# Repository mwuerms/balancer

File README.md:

# balancer
self balancing robot

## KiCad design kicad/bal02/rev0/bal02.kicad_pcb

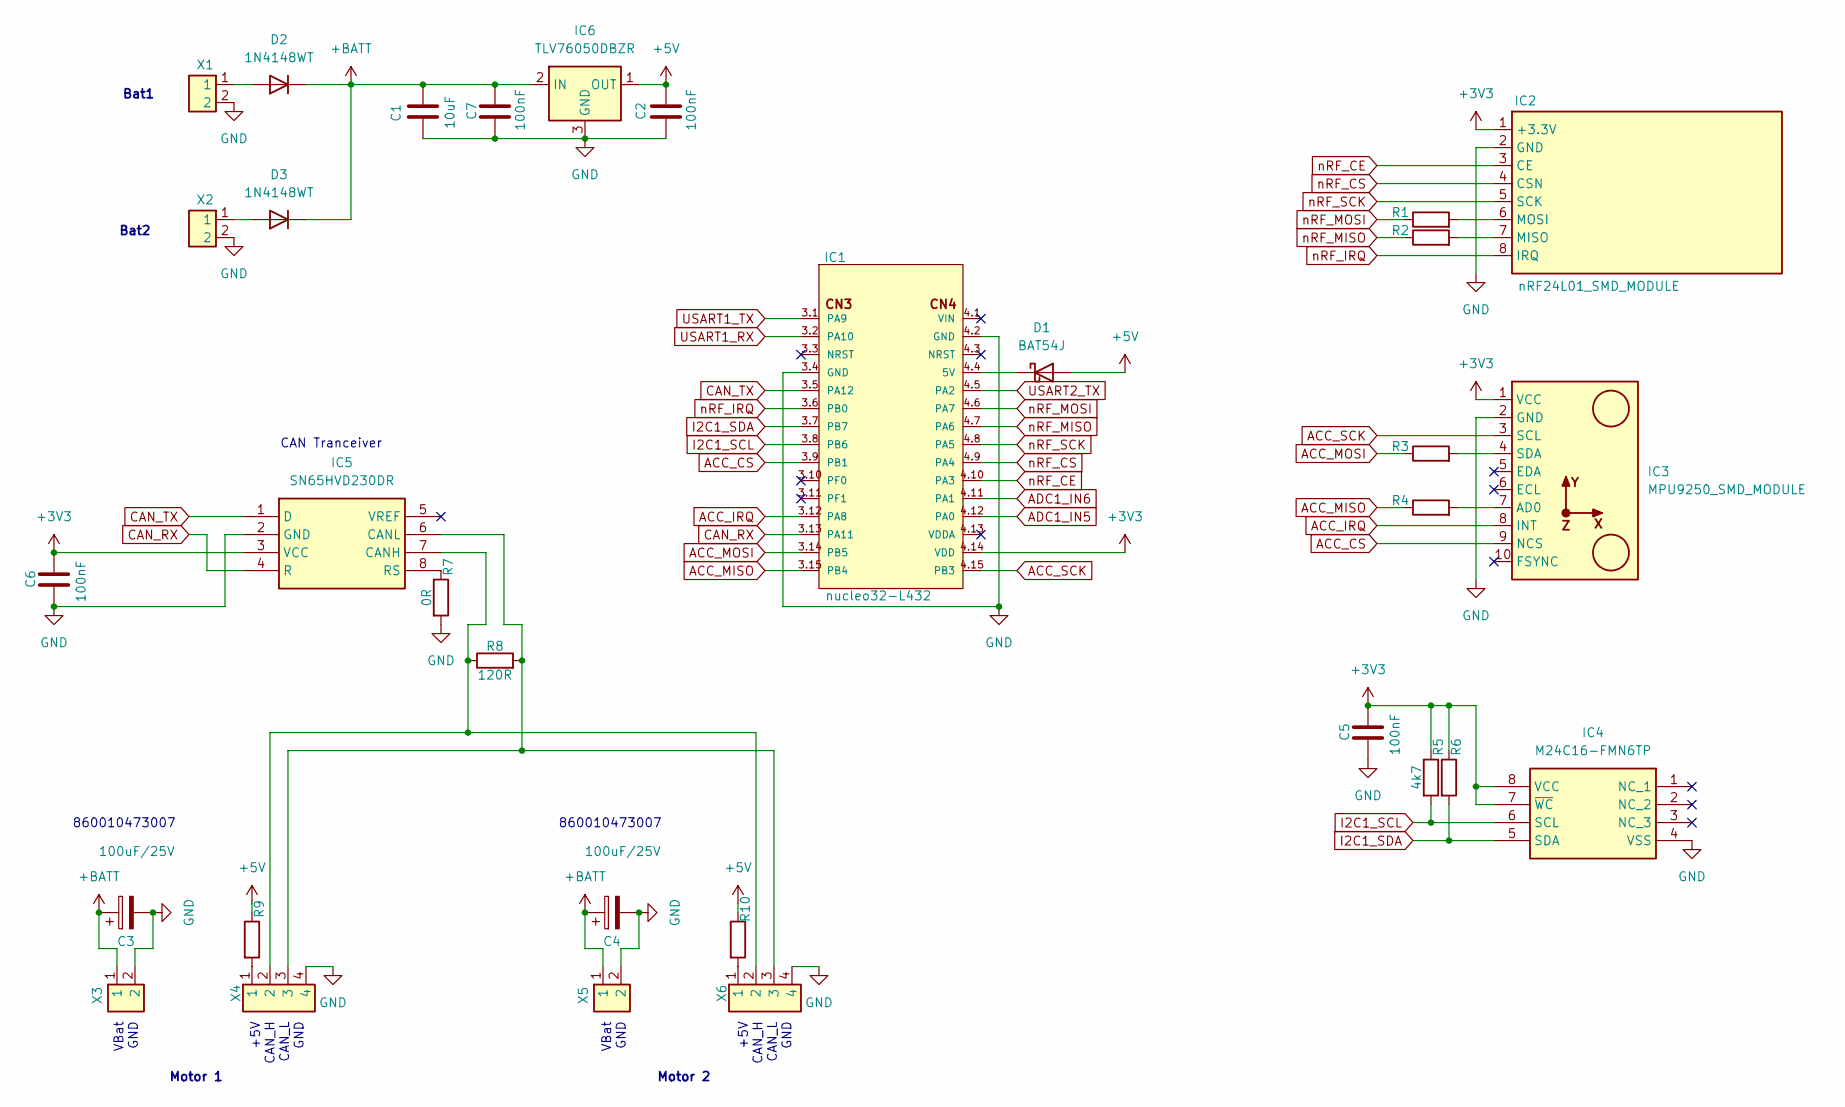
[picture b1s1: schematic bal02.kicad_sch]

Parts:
C1: 10uF; C_0805_2012Metric
C2, C5, C6, C7: 100nF; C_0603_1608Metric
C3, C4: 100uF/25V; WCAP-ATG8
D1: BAT54J; D_SOD-323F
D2, D3: 1N4148WT; D_SOD-523
IC1: nucleo32-L432; nucleo32; PARTREV 3
IC2: nRF24L01_SMD_MODULE
IC3: MPU9250_SMD_MODULE
IC4: M24C16-FMN6TP; SOIC127P600X175-8N; Manufacturer_Part_Number M24C16-FMN6TP; Mouser Part Number 511-M24C16-FMN6TP
IC5: SN65HVD230DR; SOT127P600X175-8N; Manufacturer_Part_Number SN65HVD230DR; Mouser Part Number 595-SN65HVD230DR
IC6: TLV76050DBZR; SOT95P237X112-3N; Manufacturer_Part_Number TLV76050DBZR; Mouser Part Number 595-TLV76050DBZR
R1, R2, R3, R4, R9, R10: R; R_0402_1005Metric
R5, R6: 4k7; R_0603_1608Metric
R7: 0R; R_0603_1608Metric
R8: 120R; R_0603_1608Metric
X1, X2, X3, X5: H2_100mil
X4, X6: H4_50mil

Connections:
+3V3: C5.1, C6.1, IC1.4.14 (VDD), IC2.1 (+3.3V), IC3.1 (VCC), IC4.7 (~WC), IC4.8 (VCC), IC5.3 (VCC), R5.1, R6.1
+5V: C2.1, D1.2 (A), IC6.1 (OUT), R9.1, R10.1
+BATT: C1.1, C3.1, C4.1, C7.1, D2.1 (K), D3.1 (K), IC6.2 (IN), X3.1, X5.1
ACC_CS: IC1.3.9 (PB1), IC3.9 (NCS)
ACC_IRQ: IC1.3.12 (PA8), IC3.8 (INT)
ACC_MISO: IC1.3.15 (PB4), R4.1
ACC_MOSI: IC1.3.14 (PB5), R3.1
ACC_SCK: IC1.4.15 (PB3), IC3.3 (SCL)
ADC1_IN5: IC1.4.12 (PA0)
ADC1_IN6: IC1.4.11 (PA1)
CAN_RX: IC1.3.13 (PA11), IC5.4 (R)
CAN_TX: IC1.3.5 (PA12), IC5.1 (D)
GND: C1.2, C2.2, C3.2, C4.2, C5.2, C6.2, C7.2, IC1.3.4 (GND), IC1.4.2 (GND), IC2.2 (GND), IC3.2 (GND), IC4.4 (VSS), IC5.2 (GND), IC6.3 (GND), R7.2, X1.2, X2.2, X3.2, X4.4, X5.2, X6.4
I2C1_SCL: IC1.3.8 (PB6), IC4.6 (SCL), R5.2
I2C1_SDA: IC1.3.7 (PB7), IC4.5 (SDA), R6.2
unnamed: D1.1 (K), IC1.4.4 (5V)
unnamed: D2.2 (A), X1.1
unnamed: D3.2 (A), X2.1
unnamed: IC2.7 (MISO), R2.2
unnamed: IC2.6 (MOSI), R1.2
unnamed: IC3.7 (AD0), R4.2
unnamed: IC3.4 (SDA), R3.2
unnamed: IC5.7 (CANH), R8.1, X4.2, X6.2
unnamed: IC5.6 (CANL), R8.2, X4.3, X6.3
unnamed: IC5.8 (RS), R7.1
unnamed: R9.2, X4.1
unnamed: R10.2, X6.1
USART1_RX: IC1.3.2 (PA10)
USART1_TX: IC1.3.1 (PA9)
USART2_TX: IC1.4.5 (PA2)
nRF_CE: IC1.4.10 (PA3), IC2.3 (CE)
nRF_CS: IC1.4.9 (PA4), IC2.4 (CSN)
nRF_IRQ: IC1.3.6 (PB0), IC2.8 (IRQ)
nRF_MISO: IC1.4.7 (PA6), R2.1
nRF_MOSI: IC1.4.6 (PA7), R1.1
nRF_SCK: IC1.4.8 (PA5), IC2.5 (SCK)

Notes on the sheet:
Bat2
Bat1
860010473007
+5V CAN_H CAN_L GND
VBat GND
Motor 2
CAN Tranceiver
Motor 1

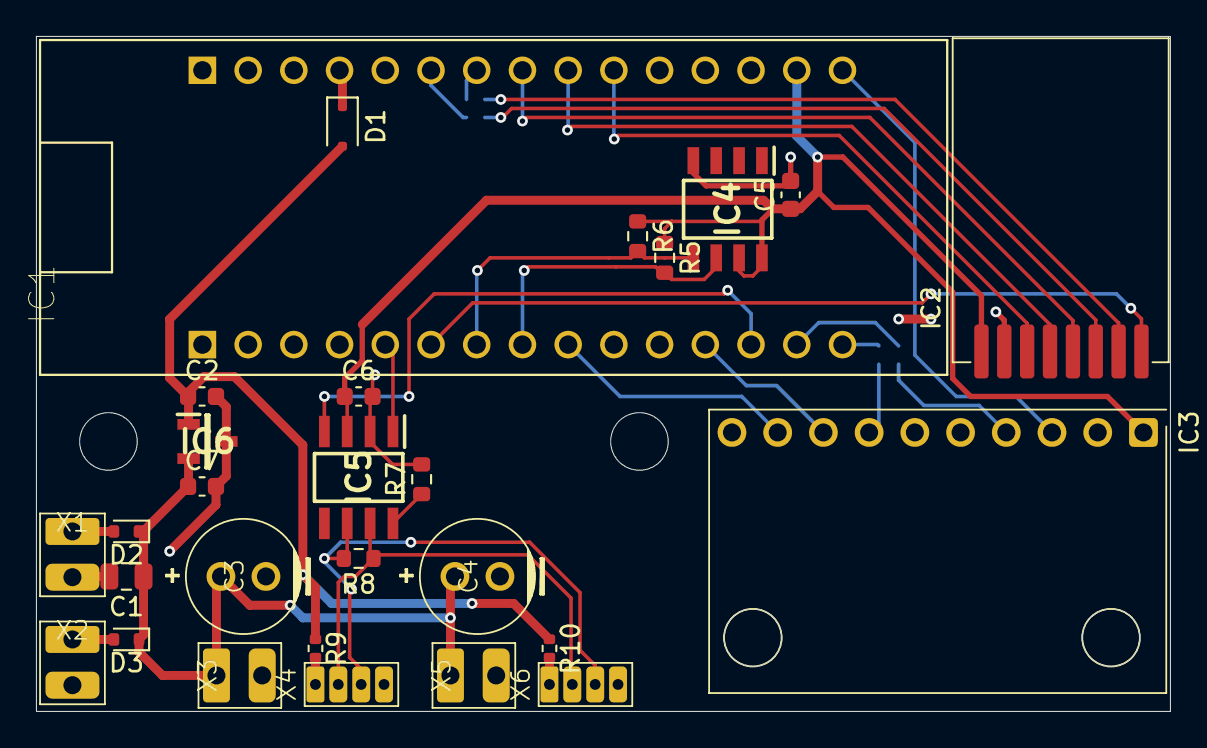
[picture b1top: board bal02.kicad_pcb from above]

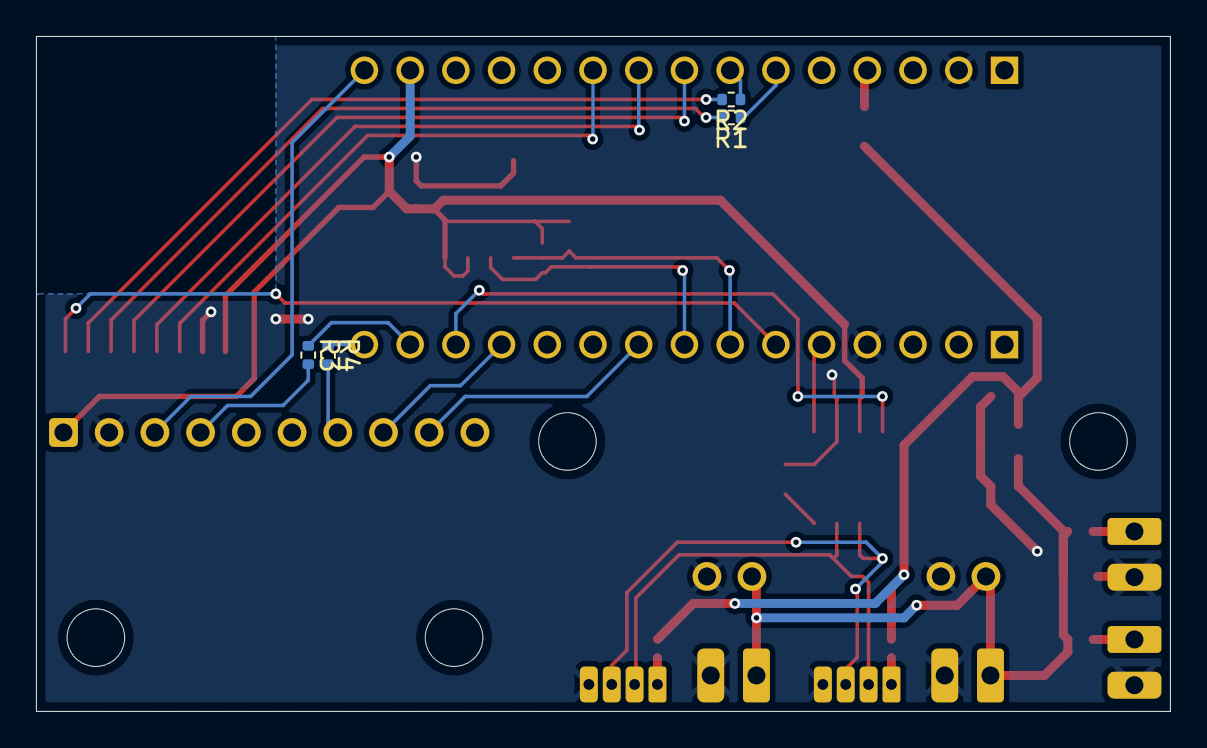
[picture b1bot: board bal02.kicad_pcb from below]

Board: 2 copper layers, 63.0 x 37.5 mm, 32 parts (4 on the bottom side), 31 nets.

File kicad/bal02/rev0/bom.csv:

Designator,Footprint,Quantity,Value,LCSC Part #
C1,0805,1,10uF,
"C2, C5, C6, C7",0603,4,100nF,
"C3, C4",WCAP-ATG8,2,100uF/25V,
D1,D_SOD-323F,1,BAT54J,
"D2, D3",D_SOD-523,2,1N4148WT,
IC1,nucleo32,1,nucleo32-L432,
IC2,nRF24L01_SMD_MODULE,1,nRF24L01_SMD_MODULE,
IC3,MPU9250_SMD_MODULE,1,MPU9250_SMD_MODULE,
IC4,SOIC127P600X175-8N,1,M24C16-FMN6TP,
IC5,SOT127P600X175-8N,1,SN65HVD230DR,
IC6,SOT95P237X112-3N,1,TLV76050DBZR,
"R1, R10, R2, R3, R4, R9",0402,6,R,
"R5, R6",0603,2,4k7,
R7,0603,1,0R,
R8,0603,1,120R,
"X1, X2, X3, X5",H2_100mil,4,~,
"X4, X6",H4_50mil,2,~,

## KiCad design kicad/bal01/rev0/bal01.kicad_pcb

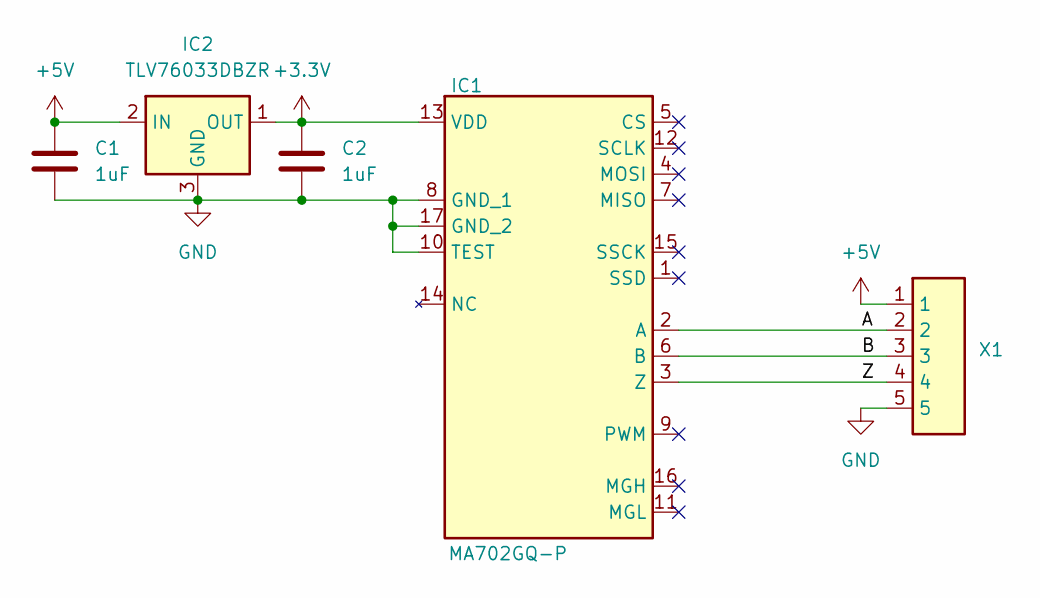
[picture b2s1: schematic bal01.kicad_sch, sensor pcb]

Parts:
C1, C2: 1uF; C_0603_1608Metric
IC1: MA702GQ-P; QFN-16; Manufacturer_Part_Number MA702GQ-P; Mouser Part Number 946-MA702GQ-P
IC2: TLV76033DBZR; SOT95P237X112-3N; Manufacturer_Part_Number TLV76050DBZR; Mouser Part Number 595-TLV76050DBZR
X1: H5_Pads_1.27mm

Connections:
+3.3V: C2.1, IC1.13 (VDD), IC2.1 (OUT)
+5V: C1.1, IC2.2 (IN), X1.1
/A: IC1.2 (A), X1.2
/B: IC1.6 (B), X1.3
/Z: IC1.3 (Z), X1.4
GND: C1.2, C2.2, IC1.8 (GND_1), IC1.10 (TEST), IC1.17 (GND_2), IC2.3 (GND), X1.5

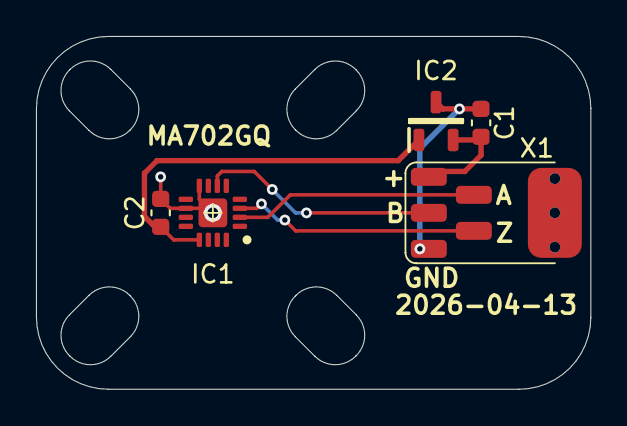
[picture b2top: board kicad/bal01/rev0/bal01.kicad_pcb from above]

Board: 2 copper layers, 30.8 x 19.6 mm, 5 parts (0 on the bottom side), 6 nets.

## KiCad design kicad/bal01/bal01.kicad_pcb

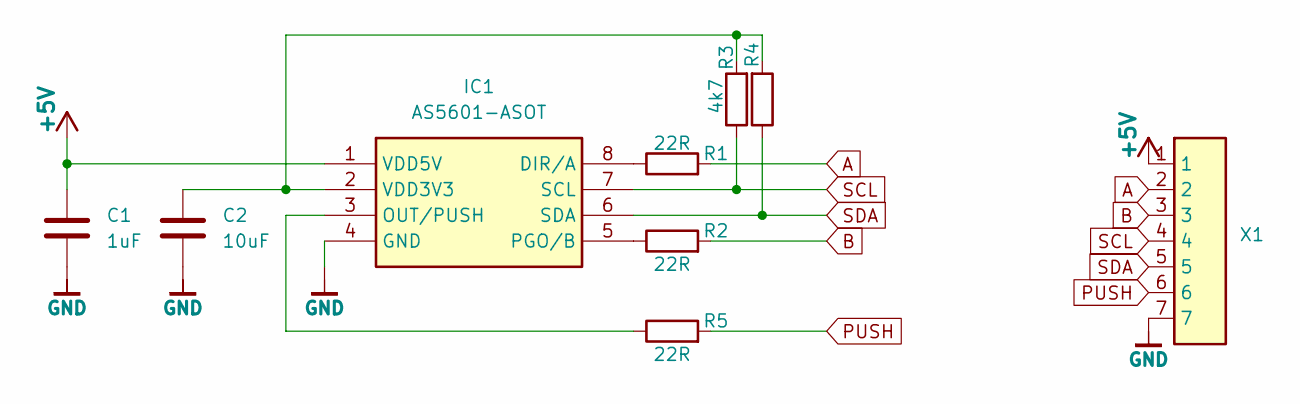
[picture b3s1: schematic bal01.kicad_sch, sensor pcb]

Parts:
C1: 1uF; C_0805_2012Metric
C2: 10uF; C_0805_2012Metric
IC1: AS5601-ASOT; SOIC127P600X175-8N; Manufacturer_Part_Number AS5600-ASOT; Mouser Part Number 985-AS5600-ASOT
R1, R2, R5: 22R; C_0603_1608Metric
R3, R4: 4k7; C_0603_1608Metric
X1: H7_Pads_1.27mm-001

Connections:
+5V: C1.1, IC1.1 (VDD5V), X1.1
A: R1.2, X1.2
B: R2.2, X1.3
GND: C1.2, C2.2, IC1.4 (GND), X1.7
unnamed: IC1.8 (DIR/A), R1.1
unnamed: IC1.3 (OUT/PUSH), R5.1
unnamed: IC1.5 (PGO/B), R2.1
unnamed: C2.1, IC1.2 (VDD3V3), R3.2, R4.2
PUSH: R5.2, X1.6
SCL: IC1.7 (SCL), R3.1, X1.4
SDA: IC1.6 (SDA), R4.1, X1.5

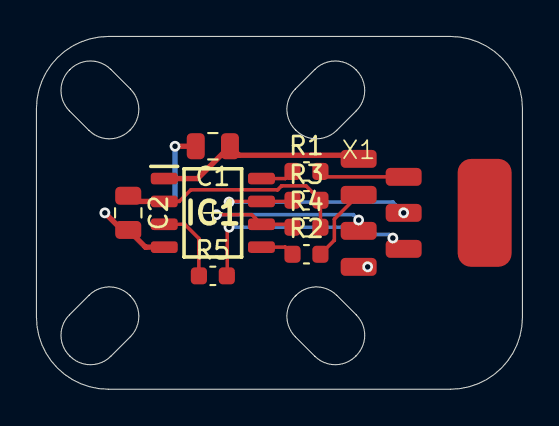
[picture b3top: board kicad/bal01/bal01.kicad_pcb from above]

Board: 2 copper layers, 27.0 x 19.6 mm, 9 parts (0 on the bottom side), 11 nets.

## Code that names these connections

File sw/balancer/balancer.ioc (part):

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Mcu.Name=STM32F103C(8-B)Tx
Mcu.Package=LQFP48
Mcu.UserName=STM32F103C8Tx
PA0-WKUP.Signal=ADCx_IN0
PA1.Signal=ADCx_IN1
PA13.Mode=Serial_Wire
PA13.Signal=SYS_JTMS-SWDIO
PA14.Mode=Serial_Wire
PA14.Signal=SYS_JTCK-SWCLK
PA2.GPIOParameters=GPIO_PuPd,GPIO_Label,GPIO_ModeDefaultEXTI
PA2.GPIO_Label=nRF_IRQ
PA2.GPIO_ModeDefaultEXTI=GPIO_MODE_IT_FALLING
PA2.GPIO_PuPd=GPIO_PULLUP
PA2.Signal=GPXTI2
PA3.GPIOParameters=GPIO_Label
PA3.GPIO_Label=nRF_CE
PA3.Signal=GPIO_Output
PA4.GPIOParameters=GPIO_Speed,PinState,GPIO_Label
PA4.GPIO_Label=nRF_CS
PA4.GPIO_Speed=GPIO_SPEED_FREQ_HIGH
PA4.PinState=GPIO_PIN_RESET
PA4.Signal=GPIO_Output
PA5.GPIOParameters=GPIO_Label
PA5.GPIO_Label=nRF_SCK
PA5.Mode=Full_Duplex_Master
PA5.Signal=SPI1_SCK
PA6.GPIOParameters=GPIO_Label
PA6.GPIO_Label=nRF_MOSI
PA6.Mode=Full_Duplex_Master
PA6.Signal=SPI1_MISO
PA7.GPIOParameters=GPIO_Label
PA7.GPIO_Label=nRF_MISO
PA7.Mode=Full_Duplex_Master
PA7.Signal=SPI1_MOSI
PA8.GPIOParameters=GPIO_PuPd,GPIO_Label
PA8.GPIO_Label=ACC_IRQ
PA8.GPIO_PuPd=GPIO_PULLUP
PA8.Signal=GPXTI8
PB0.Signal=ADCx_IN8
PB1.Signal=ADCx_IN9
PB12.GPIOParameters=GPIO_Speed,PinState,GPIO_Label
PB12.GPIO_Label=ACC_CS
PB12.GPIO_Speed=GPIO_SPEED_FREQ_HIGH
PB12.PinState=GPIO_PIN_SET
PB12.Signal=GPIO_Output
PB13.GPIOParameters=GPIO_Label
PB13.GPIO_Label=ACC_SCK
PB13.Mode=Full_Duplex_Master
PB13.Signal=SPI2_SCK
PB14.GPIOParameters=GPIO_Label
PB14.GPIO_Label=ACC_MISO
PB14.Mode=Full_Duplex_Master
PB14.Signal=SPI2_MISO
PB15.GPIOParameters=GPIO_Label
PB15.GPIO_Label=ACC_MOSI
PB15.Mode=Full_Duplex_Master
PB15.Signal=SPI2_MOSI
PB8.Mode=CAN_Activate
PB8.Signal=CAN_RX
PB9.Mode=CAN_Activate
PB9.Signal=CAN_TX
PC13-TAMPER-RTC.GPIOParameters=GPIO_Speed,GPIO_Label
PC13-TAMPER-RTC.GPIO_Label=LED
PC13-TAMPER-RTC.GPIO_Speed=GPIO_SPEED_FREQ_MEDIUM
PC13-TAMPER-RTC.Signal=GPIO_Output
PC14-OSC32_IN.Mode=LSE-External-Oscillator
PC14-OSC32_IN.Signal=RCC_OSC32_IN
PC15-OSC32_OUT.Mode=LSE-External-Oscillator
PC15-OSC32_OUT.Signal=RCC_OSC32_OUT
PD0-OSC_IN.Mode=HSE-External-Oscillator
PD0-OSC_IN.Signal=RCC_OSC_IN
PD1-OSC_OUT.Mode=HSE-External-Oscillator
PD1-OSC_OUT.Signal=RCC_OSC_OUT
RCC.SYSCLKFreq_VALUE=64000000
RCC.SYSCLKSource=RCC_SYSCLKSOURCE_PLLCLK
board=custom

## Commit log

2026-02-28 started with balancer software
2026-02-28 also starting nRF_Base
2026-02-28 nrfBase using freeRTOS
2026-03-01 nrf24 using freertos now, 1st tests: OK
2026-03-02 balancer sending -> nrfBase receiving works
2026-03-04 commom: moved common resources to folder "common"
2026-03-04 nrf24 common
2026-03-04 all works on balancer (nrf24 sender)
2026-03-04 balancer + nrfBase do work using common, also nrfBase uses uart_send_buffer + interrupt
2026-03-04 start using nrf24_msg_t
2026-03-05 started with balancer robot
2026-03-06 bal1 changed legs
2026-03-06 bal1 started with left side panel
2026-03-09 bal1 started upper cage for all the electronics
2026-03-09 bal1 added component door on the back
2026-03-09 placed rockswitch and bluepill
2026-03-10 part between the legs, upper case + door
2026-03-11 use mpu9250, added files from old project, untested
2026-03-11 added a test stand mount
2026-03-14 reading adc + mpu9250, seems to work for a start
2026-03-14 added acc ++ values to nrf24 msgs
2026-03-14 minor adjustments to between legs, print all now
2026-03-14 calculate angle and print over rf
2026-03-15 added some very basic can transmission
2026-03-28 bal2 started
2026-03-29 added missing files
2026-03-29 added balancerL432 project
2026-04-06 added MT6701 rotary sensors also started kikcad project bal01 to mount as5601 with quadrature encoder
2026-04-06 create new pcb with AS5601
2026-04-08 bal01 olmost finished
2026-04-08 bal02 Nucleo32 L432 with ACC + nRF24L01 Module
2026-04-08 more components added
2026-04-08 bal02 placement + nucleo32 update
2026-04-13 bal01 replaced sensor using MA702GQ
2026-04-13 bal01 rev0
2026-04-15 bal01, bal02 ready to order
